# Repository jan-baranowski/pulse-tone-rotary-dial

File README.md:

ATX Form Card
=============

This is the repo containig project files, production files and documentation for a pulse-to-tone (DTMF) converter for old rotary dial phones.

Complete description of this project can be found at https://patoelektronika.blogspot.com/2024/11/analog-phone-pulse-to-tone-converter.html

All the work that is not a third party documentation or libraries is licenced under WTFPLv2.

Third Party Work
================

- `doc/rotarydial` - contains firmware and documentation dump for rotarydial project  by Matthew Millman - https://www.mattmillman.com/projects/building-your-own-pulse-to-tone-converter/
- `doc/blogpost/img` - contains some third party images, whose authors are indicated in `doc/blogpost/index.html`
- `doc` also contains some PDF article dumps from Wikipedia

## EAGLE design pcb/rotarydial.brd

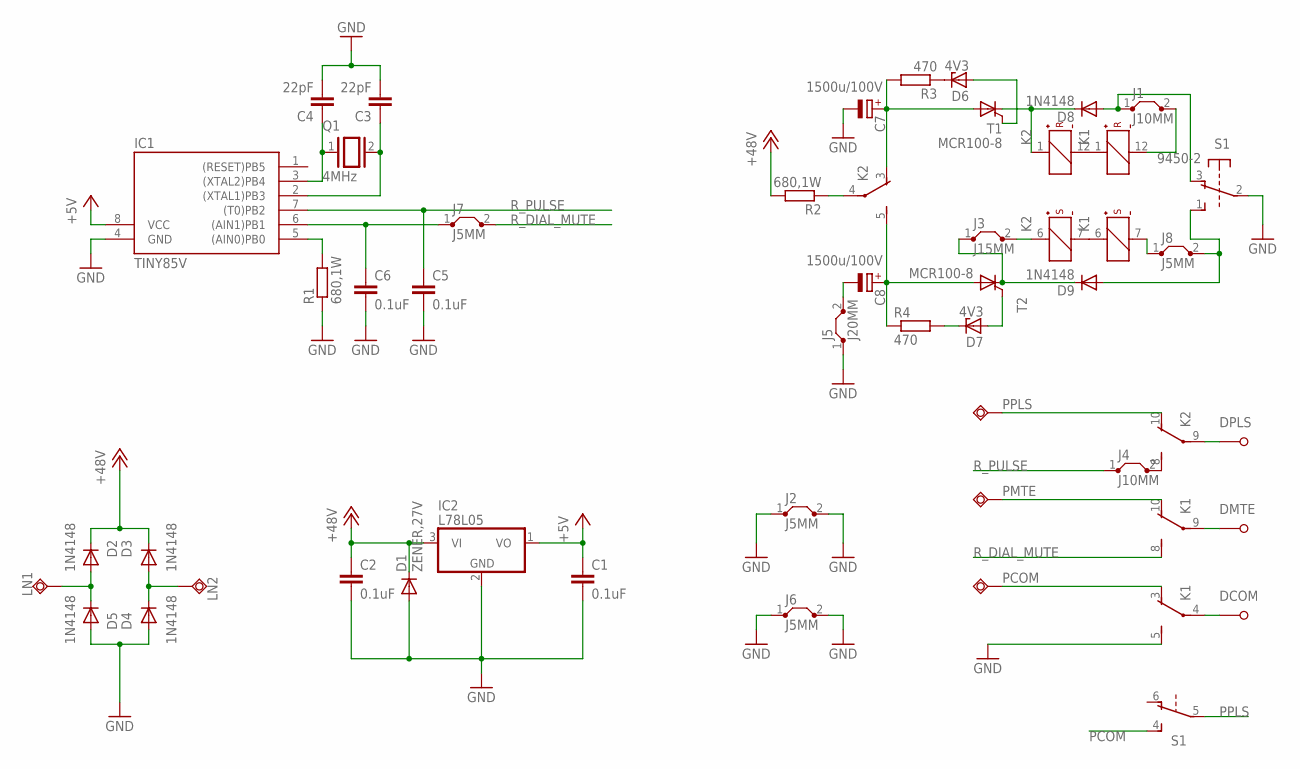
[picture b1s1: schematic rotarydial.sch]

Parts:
C1, C2, C5, C6: 0.1uF; C050-025X075
C3, C4: 22pF; C050-024X044
C7, C8: 1500u/100V; E7,5-18
D1: ZENER,27V; P2-15
D2, D3, D4, D5, D8, D9: 1N4148; DO41-10
D6, D7: 4V3; DO34Z7
DCOM: M3-SCREW-CONNECTOR
DMTE: M3-SCREW-CONNECTOR
DPLS: M3-SCREW-CONNECTOR
IC1: TINY85V; DIL08
IC2: L78L05; TO92
J1, J4: J10MM; 10
J2, J6, J7, J8: J5MM; 05
J3: J15MM; 15
J5: J20MM; 20
K1, K2: EC2-3TNU; TX2-L2
LN1, LN2: TPSQPAD1-20; P1-20
PCOM: TPSQPAD1-20; P1-20
PMTE: TPSQPAD1-20; P1-20
PPLS: TPSQPAD1-20; P1-20
Q1: 4MHz; QS
R1, R2: 680,1W; 0414V
R3, R4: 470; 0207/7
S1: 9450-2
T1, T2: MCR100-8; TO92-2

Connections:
+5V: C1.1, IC1.8 (VCC), IC2.1 (VO)
+12V: C2.1, D1.C, D2.C, D3.C, IC2.3 (VI), R2.2
GND: C1.2, C2.2, C3.2, C4.2, C5.2, C6.2, C7.-, C8.-, D1.A, D4.A, D5.A, IC1.4 (GND), IC2.2 (GND), J2.1, J2.2, J5.1, J5.2, J6.1, J6.2, K1.5 (S), R1.1, S1.2
unnamed: D2.A, D5.C, LN1.TP
unnamed: D3.A, D4.C, LN2.TP
unnamed: IC1.5 ((AIN0)PB0), R1.2
unnamed: C7.+, K2.3 (O), R3.2, T1.A
unnamed: K1.1 (+), K2.12 (-)
unnamed: J1.2, K1.12 (-)
unnamed: J3.2, K2.6 (+)
unnamed: D8.C, K2.1 (+), T1.C
unnamed: C4.1, IC1.3 ((XTAL2)PB4), Q1.1
unnamed: DPLS.P$1, DPLS.P$2, DPLS.P$3, DPLS.P$4, K2.9
unnamed: K1.6 (+), K2.7 (-)
unnamed: C3.1, IC1.2 ((XTAL1)PB3), Q1.2
unnamed: D9.C, J3.1, T2.C
unnamed: C8.+, K2.5 (S), R4.1, T2.A
unnamed: J8.1, K1.7 (-)
unnamed: D9.A, J8.2, S1.1 (S)
unnamed: DMTE.P$1, DMTE.P$2, DMTE.P$3, DMTE.P$4, K1.9
unnamed: DCOM.P$1, DCOM.P$2, DCOM.P$3, DCOM.P$4, K1.4
unnamed: D6.C, R3.1
unnamed: D7.C, R4.2
unnamed: D6.A, T1.G
unnamed: D7.A, T2.G
unnamed: D8.A, J1.1, S1.3 (O)
unnamed: J4.2, K2.8 (S)
PCOM: K1.3 (O), PCOM.TP, S1.4 (S)
PMTE: K1.10 (O), PMTE.TP
PPLS: K2.10 (O), PPLS.TP, S1.5
R2: K2.4, R2.1
R_DIAL_MUTE: C6.1, IC1.6 ((AIN1)PB1), J7.1, J7.2, K1.8 (S)
R_PULSE: C5.1, IC1.7 ((T0)PB2), J4.1

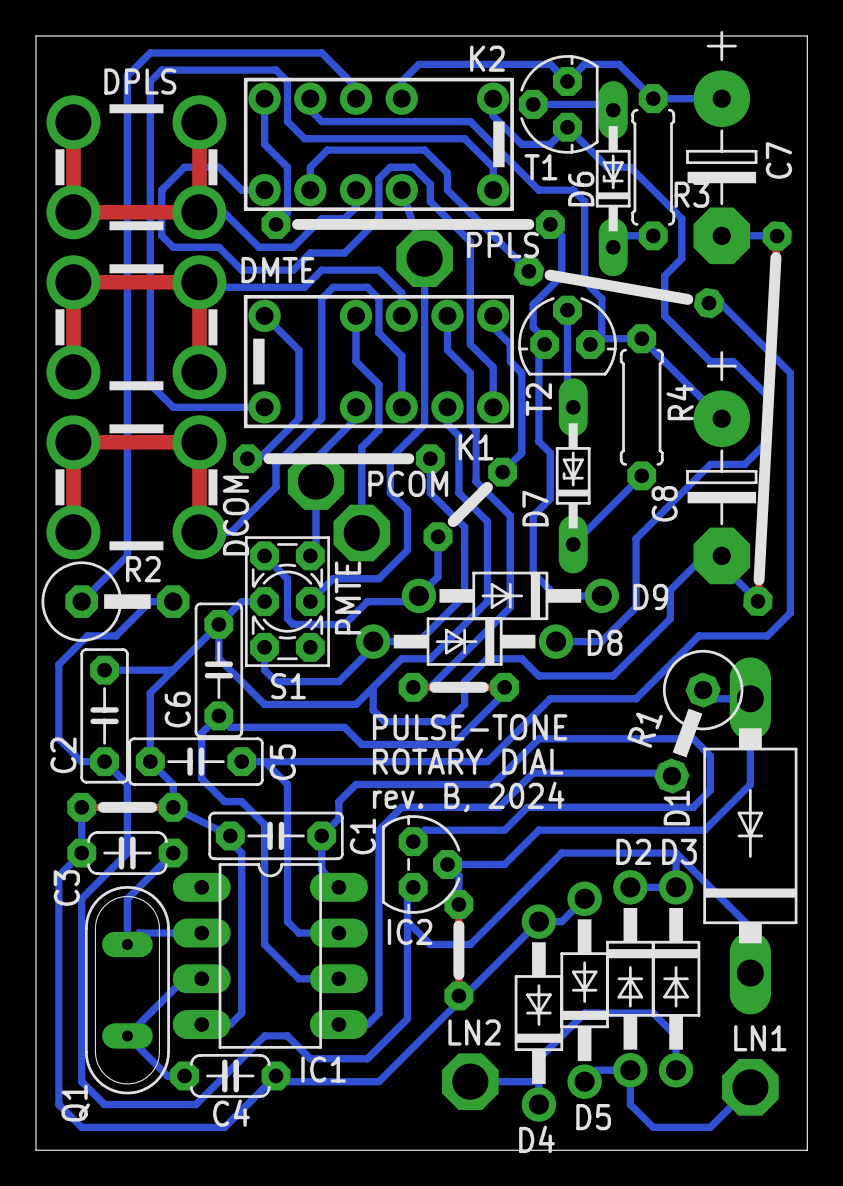
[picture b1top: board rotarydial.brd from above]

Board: 2 copper layers, 42.9 x 61.9 mm, 45 parts (0 on the bottom side), 33 nets.

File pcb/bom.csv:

Part;Value;Device;Package;Description
C1;0.1uF;C-EU050-025X075;C050-025X075;
C2;0.1uF;C-EU050-025X075;C050-025X075;
C3;22pF;C-EU050-024X044;C050-024X044;
C4;22pF;C-EU050-024X044;C050-024X044;
C5;0.1uF;C-EU050-025X075;C050-025X075;
C6;0.1uF;C-EU050-025X075;C050-025X075;
C7;1500u/100V;CPOL-EUE7.5-18;E7,5-18;
C8;1500u/100V;CPOL-EUE7.5-18;E7,5-18;
D1;ZENER,27V;DIODE-P2-15;P2-15;
D2;1N4148;1N4933;DO41-10;
D3;1N4148;1N4933;DO41-10;
D4;1N4148;1N4933;DO41-10;
D5;1N4148;1N4933;DO41-10;
D6;4V3;BZV10;DO34Z7;Z DIODE
D7;4V3;BZV10;DO34Z7;Z DIODE
D8;1N4148;1N4933;DO41-10;
D9;1N4148;1N4933;DO41-10;
DCOM;M3-SCREW-CONNECTOR;M3-SCREW-CONNECTOR;M3-SCREW-CONNECTOR;A98R, https://audiodesign.info.pl/srubki-i-nakretki/ZLACZE-SRUBOWE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
DMTE;M3-SCREW-CONNECTOR;M3-SCREW-CONNECTOR;M3-SCREW-CONNECTOR;A98R, https://audiodesign.info.pl/srubki-i-nakretki/ZLACZE-SRUBOWE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
DPLS;M3-SCREW-CONNECTOR;M3-SCREW-CONNECTOR;M3-SCREW-CONNECTOR;A98R, https://audiodesign.info.pl/srubki-i-nakretki/ZLACZE-SRUBOWE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
IC1;TINY85V;TINY10P;DIL08;MICROCONTROLLER
IC2;L78L05;L78L05;TO92;
J1;J10MM;J10MM;10;Wire Bridge, 26-28AWG
J2;J5MM;J5MM;5;Wire Bridge, 26-28AWG
J3;J15MM;J15MM;15;Wire Bridge, 26-28AWG
J4;J10MM;J10MM;10;Wire Bridge, 26-28AWG
J5;J20MM;J20MM;20;Wire Bridge, 26-28AWG
J6;J5MM;J5MM;5;Wire Bridge, 26-28AWG
J7;J5MM;J5MM;5;Wire Bridge, 26-28AWG
J8;J5MM;J5MM;5;Wire Bridge, 26-28AWG
K1;EC2-3TNU;EC2-3TNU;EC2-3TNU;
K2;EC2-3TNU;EC2-3TNU;EC2-3TNU;
LN1;TPSQPAD1-20;TPSQPAD1-20;P1-20;Test pad
LN2;TPSQPAD1-20;TPSQPAD1-20;P1-20;Test pad
PCOM;TPSQPAD1-20;TPSQPAD1-20;P1-20;Test pad
PMTE;TPSQPAD1-20;TPSQPAD1-20;P1-20;Test pad
PPLS;TPSQPAD1-20;TPSQPAD1-20;P1-20;Test pad
Q1;4MHz;XTAL/S;QS;
R1;680,1W;R-EU_0414/5V;0414V;Vertically mounted
R2;680,1W;R-EU_0414/5V;0414V;Vertically mounted
R3;470;R-EU_0207/7;0207/7;
R4;470;R-EU_0207/7;0207/7;
S1;9450-2;9450-2;9450-2;MARQUARDT SWITCH or 2x3 2,54 PIN HEADER
T1;MCR100-8;MCR100-8;TO92-2;THYRISTOR
T2;MCR100-8;MCR100-8;TO92-2;THYRISTOR

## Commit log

2024-11-22 Revision A of the board.
2024-11-22 Updated .gitignore file to exclude previous versions of EAGLE's schematics, board and library files.
2024-11-22 Added/updated documentation.
2024-11-26 Added gerber files for board rev. A.
2024-11-30 Added Blogspot post copy describing details of this device. That post should be considered an official documentation.
2024-11-30 Added basic README and license file.
2024-12-12 Fixed one of blog post images' location.
2024-12-12 Fixed some design errors of board rev. A. This is now officially board rev. B.
2024-12-12 Added Gerber files for board rev. B.
2024-12-12 Moved EAGLE6 libraries to the correct dir.
2024-12-12 Fixed layer display for board design.
2024-12-12 Silkscreen now does not contain arrows with dimensions.
2024-12-13 Updated list of third party works in documentation.
2024-12-13 Added bill of materials for board rev. B.
2024-12-13 Updated blog post/documentation to the current version.
2024-12-16 Added the last one missing video from documentation/blog post.
